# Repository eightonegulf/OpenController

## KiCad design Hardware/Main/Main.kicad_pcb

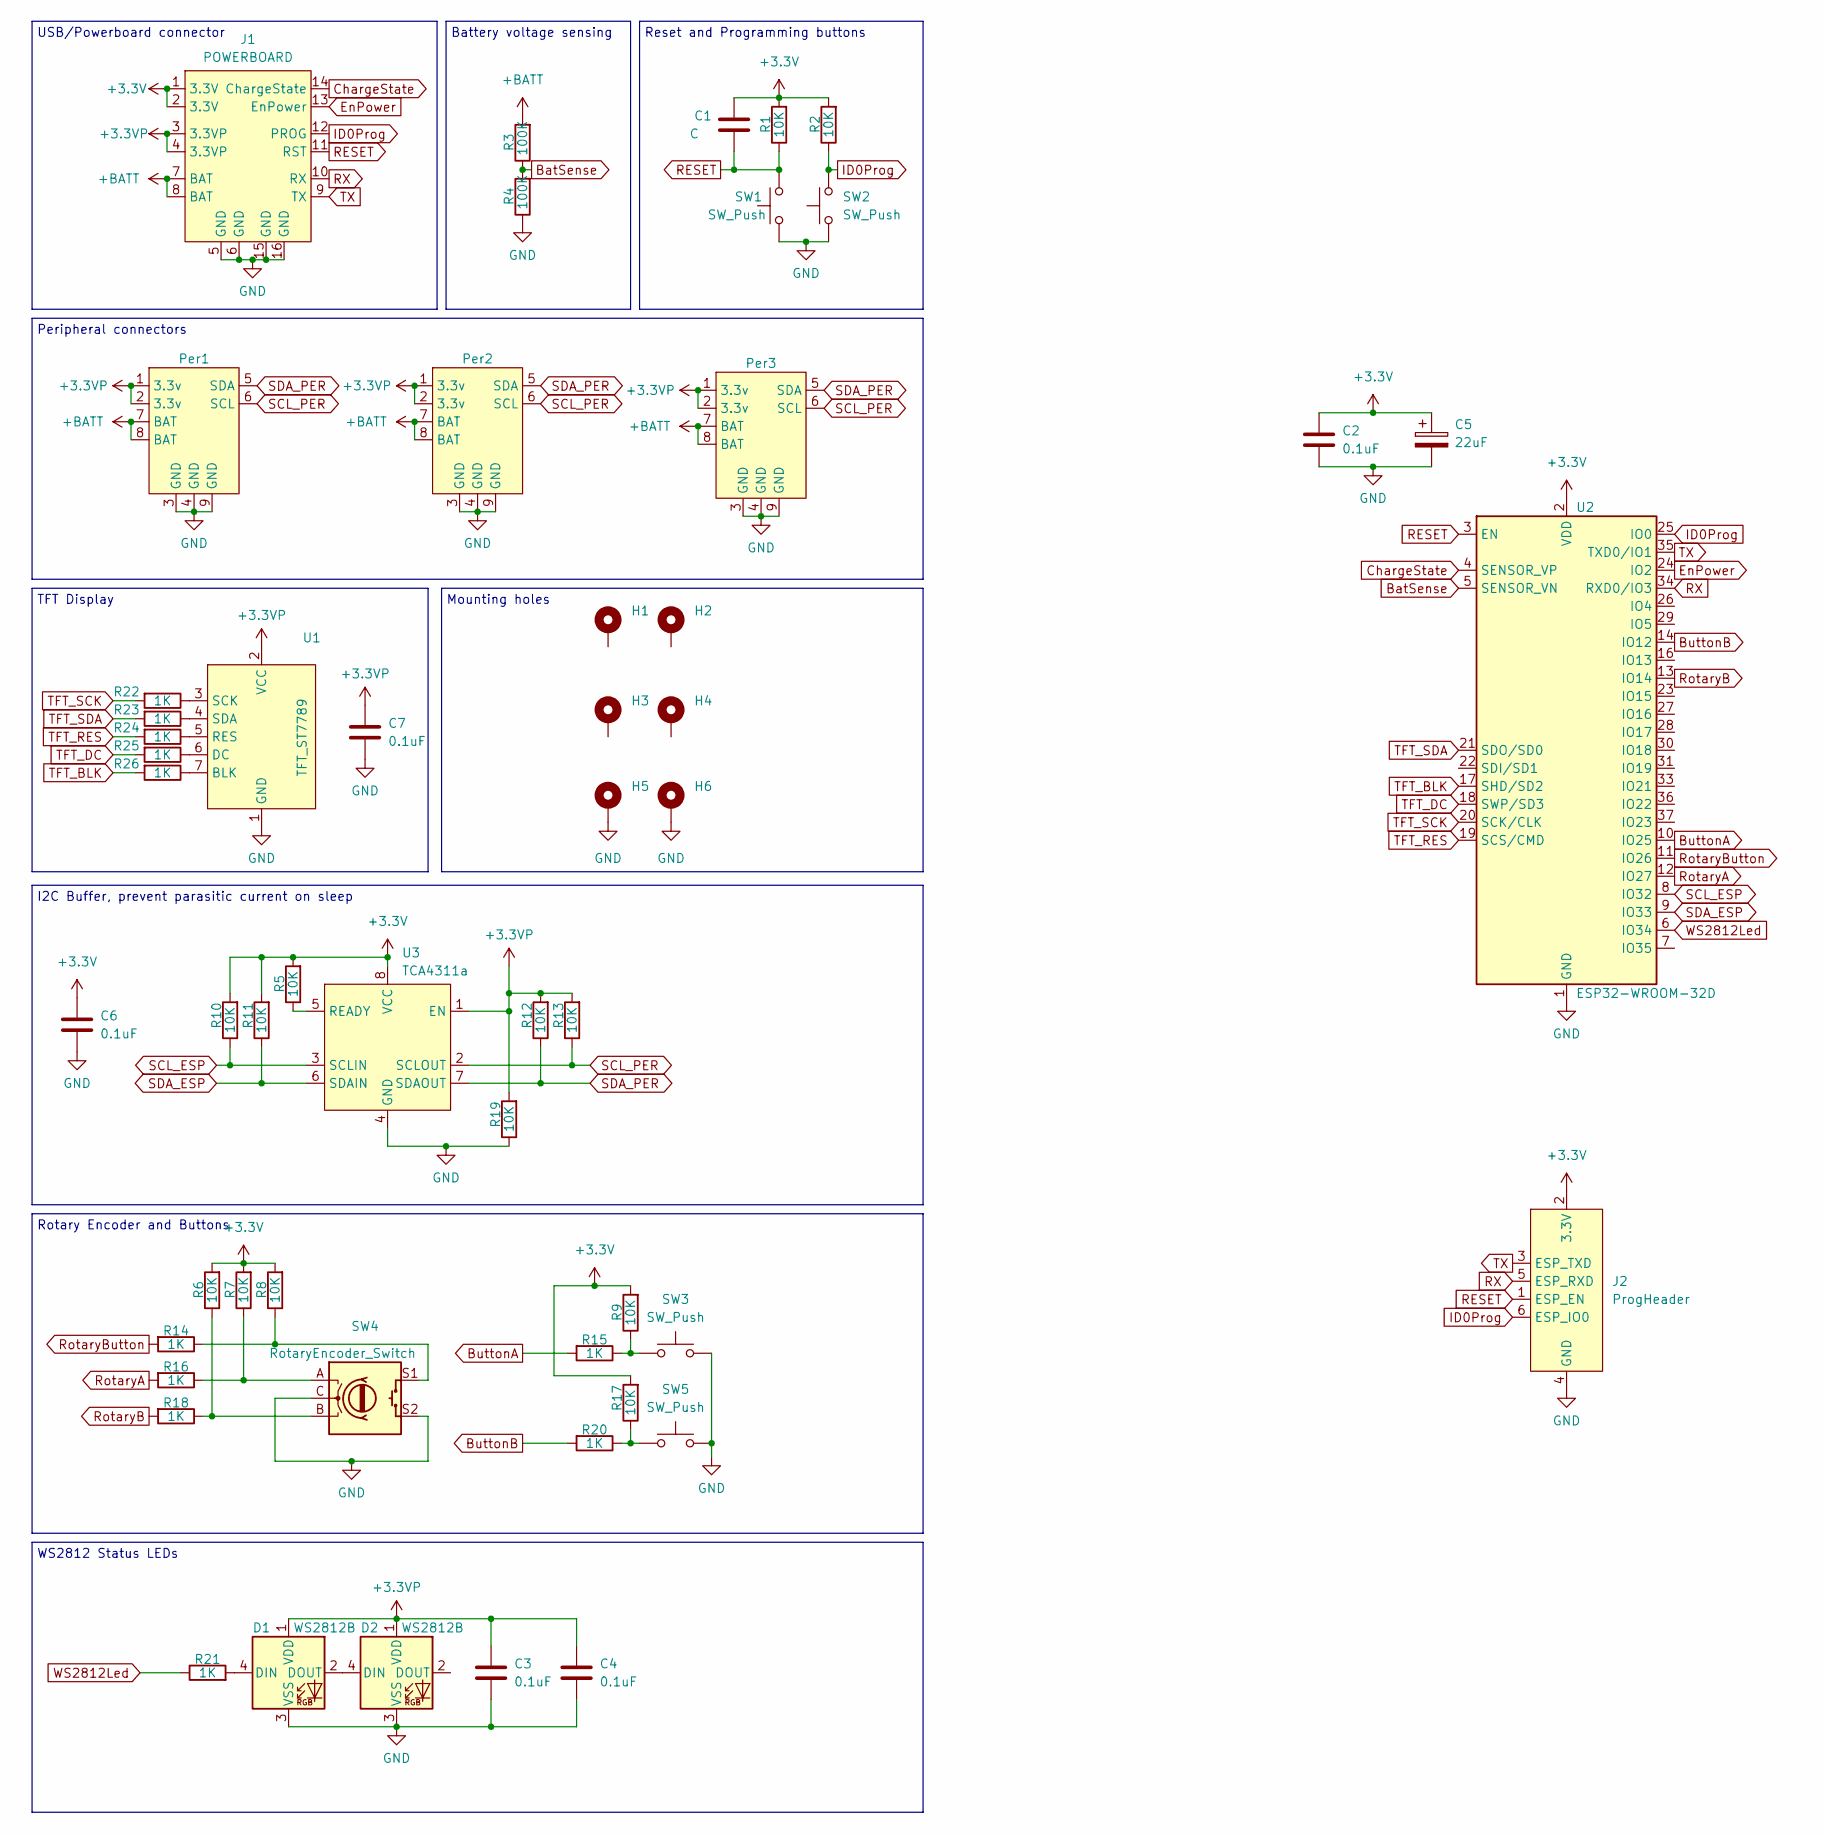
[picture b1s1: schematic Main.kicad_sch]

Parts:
C1: C; C_0805_2012Metric_Pad1.18x1.45mm_HandSolder
C2, C3, C4, C6, C7: 0.1uF; C_0805_2012Metric_Pad1.18x1.45mm_HandSolder
C5: 22uF; CP_Elec_4x5.3
D1, D2: WS2812B; LED_WS2812B_PLCC4_5.0x5.0mm_P3.2mm
H1, H2: MountingHole_Pad; MountingHole_2.2mm_M2_DIN965_Pad
H3, H4, H5, H6: MountingHole_Pad; MountingHole_3.2mm_M3_DIN965_Pad
J1: POWERBOARD; PowerBoardConsumer
J2: ProgHeader; ESP32ProgHeader
Per1: PeripheralMaster
Per2: PeripheralMaster_Right
Per3: PeripheralMaster_Left
R1, R2, R5, R6, R7, R8, R9, R10, R11, R12, R13, R17, R19: 10K; R_0805_2012Metric_Pad1.20x1.40mm_HandSolder
R3, R4: 100K; R_0805_2012Metric_Pad1.20x1.40mm_HandSolder
R14, R15, R16, R18, R20, R21, R22, R23, R24, R25, R26: 1K; R_0805_2012Metric_Pad1.20x1.40mm_HandSolder
SW1, SW2: SW_Push; SW_SPST_TL3305A
SW3, SW5: SW_Push; SW_PUSH_6mm_H8mm
SW4: RotaryEncoder_Switch; RotaryEncoder_Alps_EC11E-Switch_Vertical_H20mm
U1: TFT_ST7789; RGB_TFT_1.3
U2: ESP32-WROOM-32D
U3: TCA4311a; SOIC-8_3.9x4.9mm_P1.27mm

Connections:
+3.3V: C1.2, C2.1, C5.1, C6.1, J1.1 (3.3V), J1.2 (3.3V), J2.2 (3.3V), R1.2, R2.2, R5.2, R6.2, R7.2, R8.2, R9.2, R10.2, R11.2, R17.2, U2.2 (VDD), U3.8 (VCC)
+3.3VP: C3.1, C4.1, C7.1, D1.1 (VDD), D2.1 (VDD), J1.3 (3.3VP), J1.4 (3.3VP), Per1.1 (3.3v), Per1.2 (3.3v), Per2.1 (3.3v), Per2.2 (3.3v), Per3.1 (3.3v), Per3.2 (3.3v), R12.2, R13.2, R19.2, U1.2 (VCC), U3.1 (EN)
+BATT: J1.7 (BAT), J1.8 (BAT), Per1.7 (BAT), Per1.8 (BAT), Per2.7 (BAT), Per2.8 (BAT), Per3.7 (BAT), Per3.8 (BAT), R3.2
BatSense: R3.1, R4.2, U2.5 (SENSOR_VN)
ButtonA: R15.2, U2.10 (IO25)
ButtonB: R20.2, U2.14 (IO12)
ChargeState: J1.14 (ChargeState), U2.4 (SENSOR_VP)
EnPower: J1.13 (EnPower), U2.24 (IO2)
GND: C2.2, C3.2, C4.2, C5.2, C6.2, C7.2, D1.3 (VSS), D2.3 (VSS), H5.1, H6.1, J1.5 (GND), J1.6 (GND), J1.15 (GND), J1.16 (GND), J2.4 (GND), Per1.3 (GND), Per1.4 (GND), Per1.9 (GND), Per2.3 (GND), Per2.4 (GND), Per2.9 (GND), Per3.3 (GND), Per3.4 (GND), Per3.9 (GND), R4.1, R19.1, SW1.1, SW2.1, SW3.2, SW4.C, SW4.S2, SW5.2, U1.1 (GND), U2.1 (GND), U2.15 (GND), U2.38 (GND), U2.39 (GND), U3.4 (GND)
ID0Prog: J1.12 (PROG), J2.6 (ESP_IO0), R2.1, SW2.2, U2.25 (IO0)
unnamed: D1.4 (DIN), R21.2
unnamed: D1.2 (DOUT), D2.4 (DIN)
unnamed: R8.1, R14.1, SW4.S1
unnamed: R9.1, R15.1, SW3.1
unnamed: R7.1, R16.1, SW4.A
unnamed: R17.1, R20.1, SW5.1
unnamed: R6.1, R18.1, SW4.B
unnamed: R26.1, U1.7 (BLK)
unnamed: R25.1, U1.6 (DC)
unnamed: R24.1, U1.5 (RES)
unnamed: R22.1, U1.3 (SCK)
unnamed: R23.1, U1.4 (SDA)
unnamed: R5.1, U3.5 (READY)
RESET: C1.1, J1.11 (RST), J2.1 (ESP_EN), R1.1, SW1.2, U2.3 (EN)
RX: J1.10 (RX), J2.5 (ESP_RXD), U2.34 (RXD0/IO3)
RotaryA: R16.2, U2.12 (IO27)
RotaryB: R18.2, U2.13 (IO14)
RotaryButton: R14.2, U2.11 (IO26)
SCL_ESP: R10.1, U2.8 (IO32), U3.3 (SCLIN)
SCL_PER: Per1.6 (SCL), Per2.6 (SCL), Per3.6 (SCL), R13.1, U3.2 (SCLOUT)
SDA_ESP: R11.1, U2.9 (IO33), U3.6 (SDAIN)
SDA_PER: Per1.5 (SDA), Per2.5 (SDA), Per3.5 (SDA), R12.1, U3.7 (SDAOUT)
TFT_BLK: R26.2, U2.17 (SHD/SD2)
TFT_DC: R25.2, U2.18 (SWP/SD3)
TFT_RES: R24.2, U2.19 (SCS/CMD)
TFT_SCK: R22.2, U2.20 (SCK/CLK)
TFT_SDA: R23.2, U2.21 (SDO/SD0)
TX: J1.9 (TX), J2.3 (ESP_TXD), U2.35 (TXD0/IO1)
WS2812Led: R21.1, U2.6 (IO34)

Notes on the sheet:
Mounting holes
Peripheral connectors
Reset and Programming buttons
WS2812 Status LEDs
TFT Display
I2C Buffer, prevent parasitic current on sleep
USB/Powerboard connector
Rotary Encoder and Buttons
Battery voltage sensing

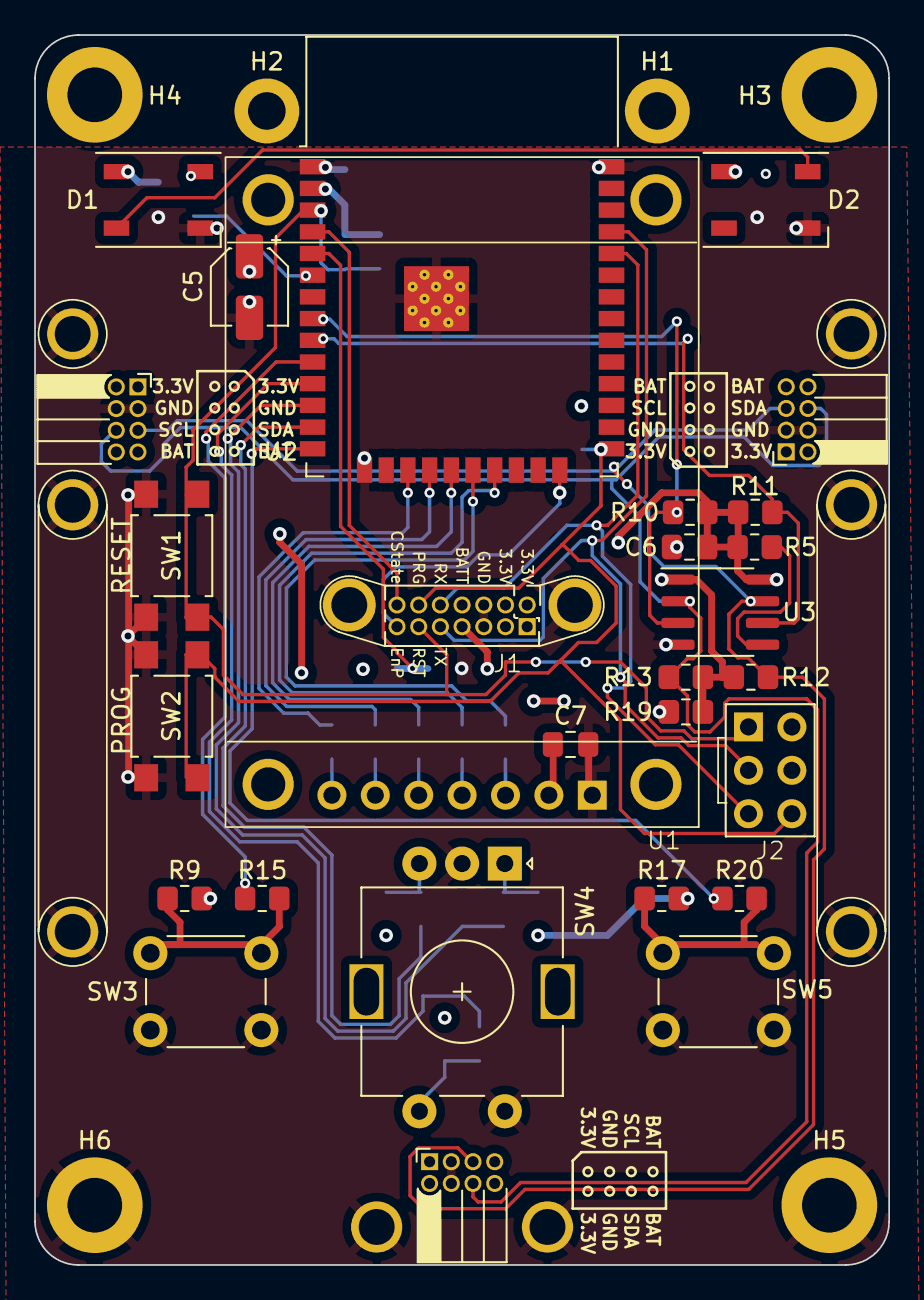
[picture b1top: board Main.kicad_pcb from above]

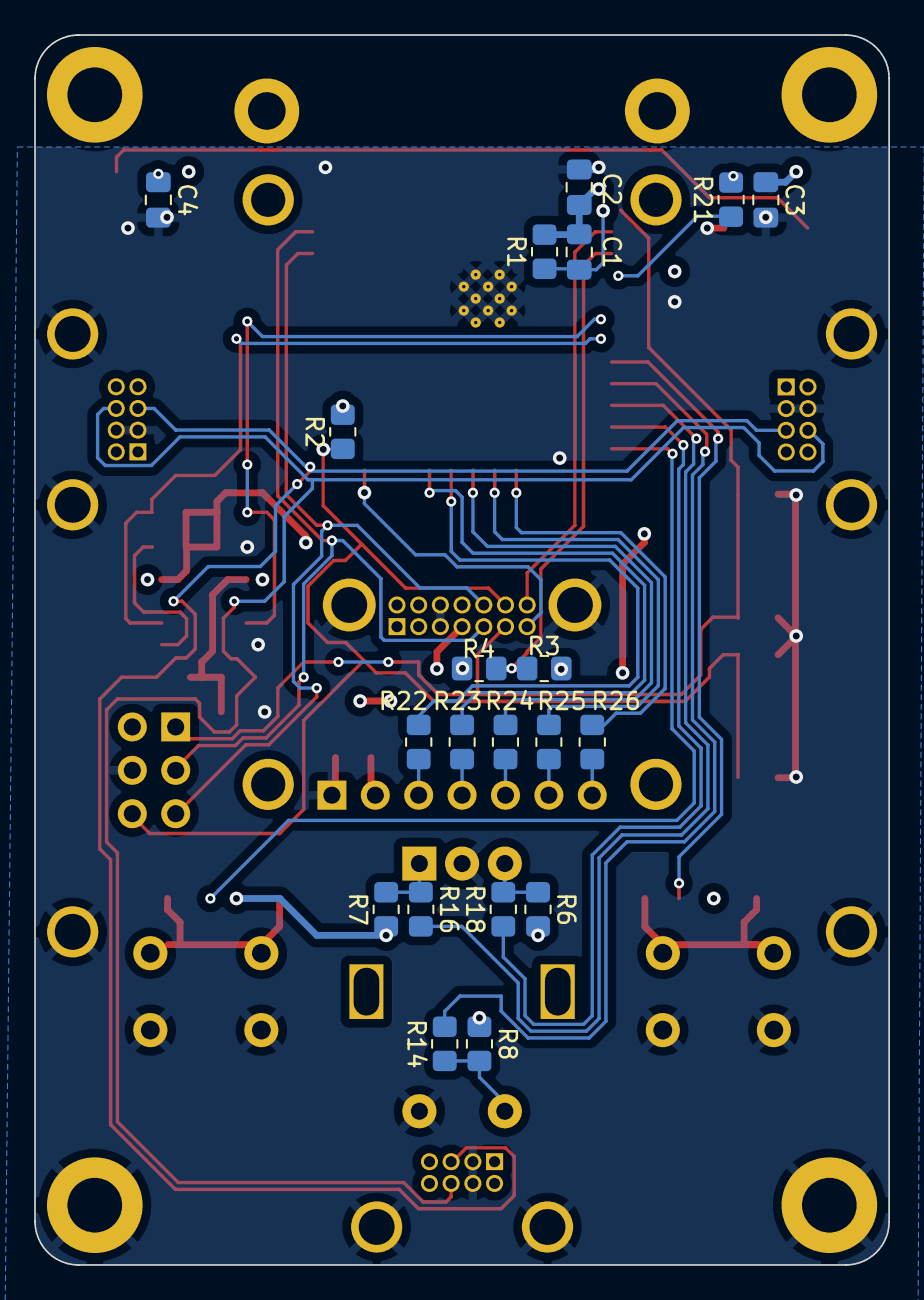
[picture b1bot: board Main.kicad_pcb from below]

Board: 4 copper layers, 50.0 x 72.0 mm, 54 parts (20 on the bottom side), 39 nets.

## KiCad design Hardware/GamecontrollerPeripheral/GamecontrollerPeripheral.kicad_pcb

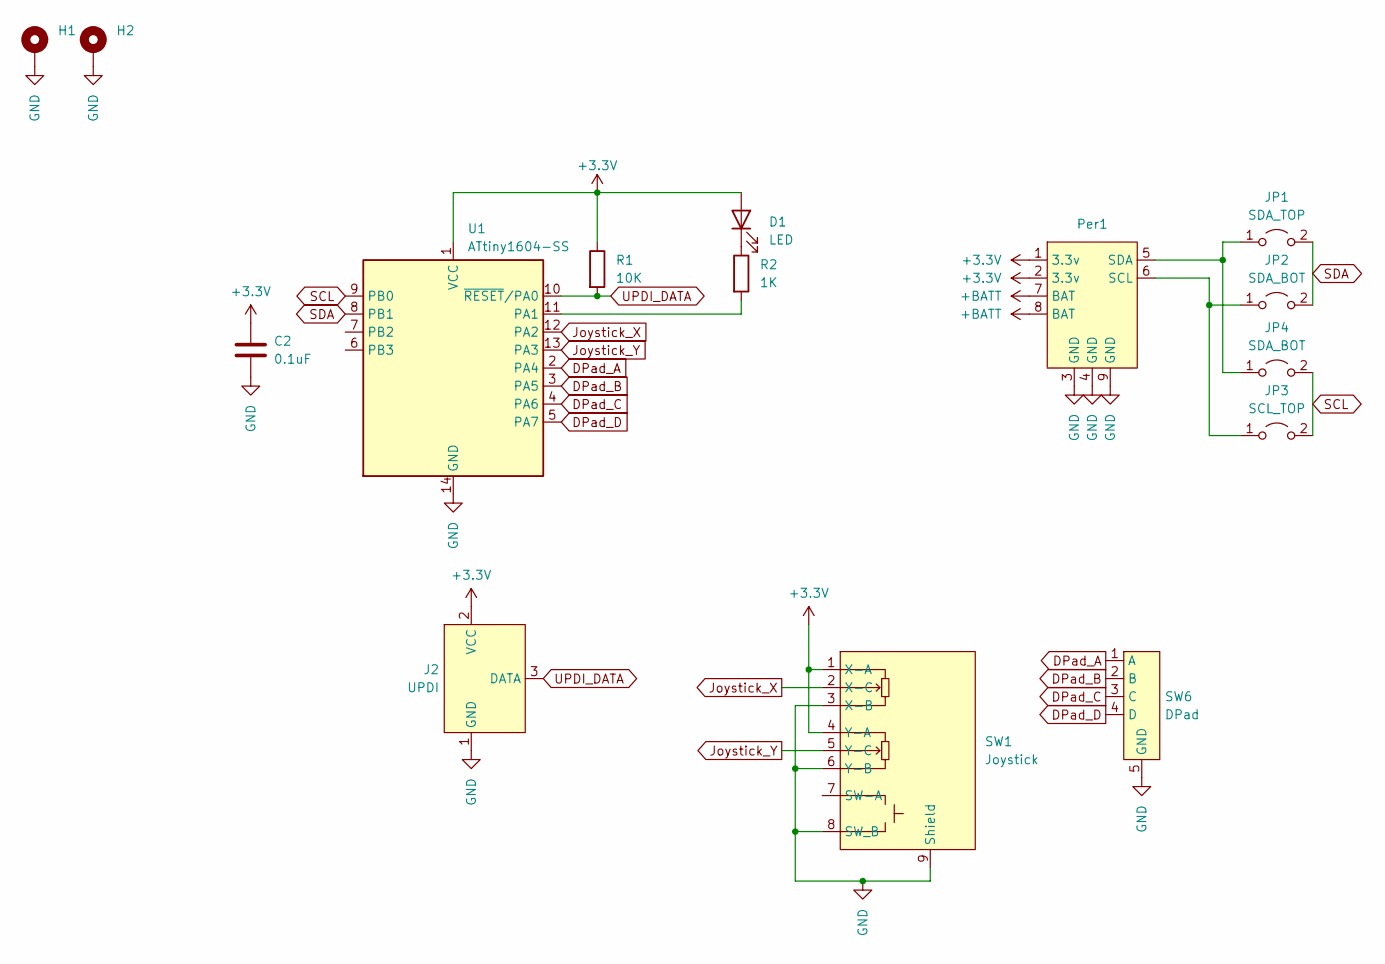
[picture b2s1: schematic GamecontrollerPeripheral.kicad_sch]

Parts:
C2: 0.1uF; C_0805_2012Metric_Pad1.18x1.45mm_HandSolder
D1: LED; LED_0805_2012Metric_Pad1.15x1.40mm_HandSolder
H1, H2: MountingHole_Pad; MountingHole_2.2mm_M2_DIN965_Pad
J2: UPDI; PinHeader_1x03_P2.54mm_Vertical
JP1: SDA_TOP; SolderJumper-2_P1.3mm_Open_RoundedPad1.0x1.5mm
JP2, JP4: SDA_BOT; SolderJumper-2_P1.3mm_Open_RoundedPad1.0x1.5mm
JP3: SCL_TOP; SolderJumper-2_P1.3mm_Open_RoundedPad1.0x1.5mm
Per1: PeripheralSlave
R1: 10K; R_0805_2012Metric_Pad1.20x1.40mm_HandSolder
R2: 1K; R_0805_2012Metric_Pad1.20x1.40mm_HandSolder
SW1: Joystick; Joystick-Universal
SW6: DPad; D-Pad
U1: ATtiny1604-SS; SOIC-14_3.9x8.7mm_P1.27mm

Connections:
+3.3V: D1.2 (A), J2.2 (VCC), Per1.1 (3.3v), Per1.2 (3.3v), R1.1, SW1.1 (X-A), SW1.4 (Y-A), U1.1 (VCC); also elsewhere on the board
+BATT: Per1.7 (BAT), Per1.8 (BAT)
DPad_A: SW6.1 (A), U1.2 (PA4)
DPad_B: SW6.2 (B), U1.3 (PA5)
DPad_C: SW6.3 (C), U1.4 (PA6)
DPad_D: SW6.4 (D), U1.5 (PA7)
GND: H1.1, H2.1, J2.1 (GND), Per1.3 (GND), Per1.4 (GND), Per1.9 (GND), SW1.3 (X-B), SW1.6 (Y-B), SW1.8 (SW_B), SW1.9 (Shield), SW6.5 (GND), U1.14 (GND); also elsewhere on the board
Joystick_X: SW1.2 (X-C), U1.12 (PA2)
Joystick_Y: SW1.5 (Y-C), U1.13 (PA3)
unnamed: D1.1 (K), R2.1
unnamed: JP1.1 (A), JP4.1 (A), Per1.5 (SDA)
unnamed: JP2.1 (A), JP3.1 (A), Per1.6 (SCL)
unnamed: R2.2, U1.11 (PA1)
SCL: JP3.2 (B), JP4.2 (B), U1.9 (PB0)
SDA: JP1.2 (B), JP2.2 (B), U1.8 (PB1)
UPDI_DATA: J2.3 (DATA), R1.2, U1.10 (~RESET/PA0)

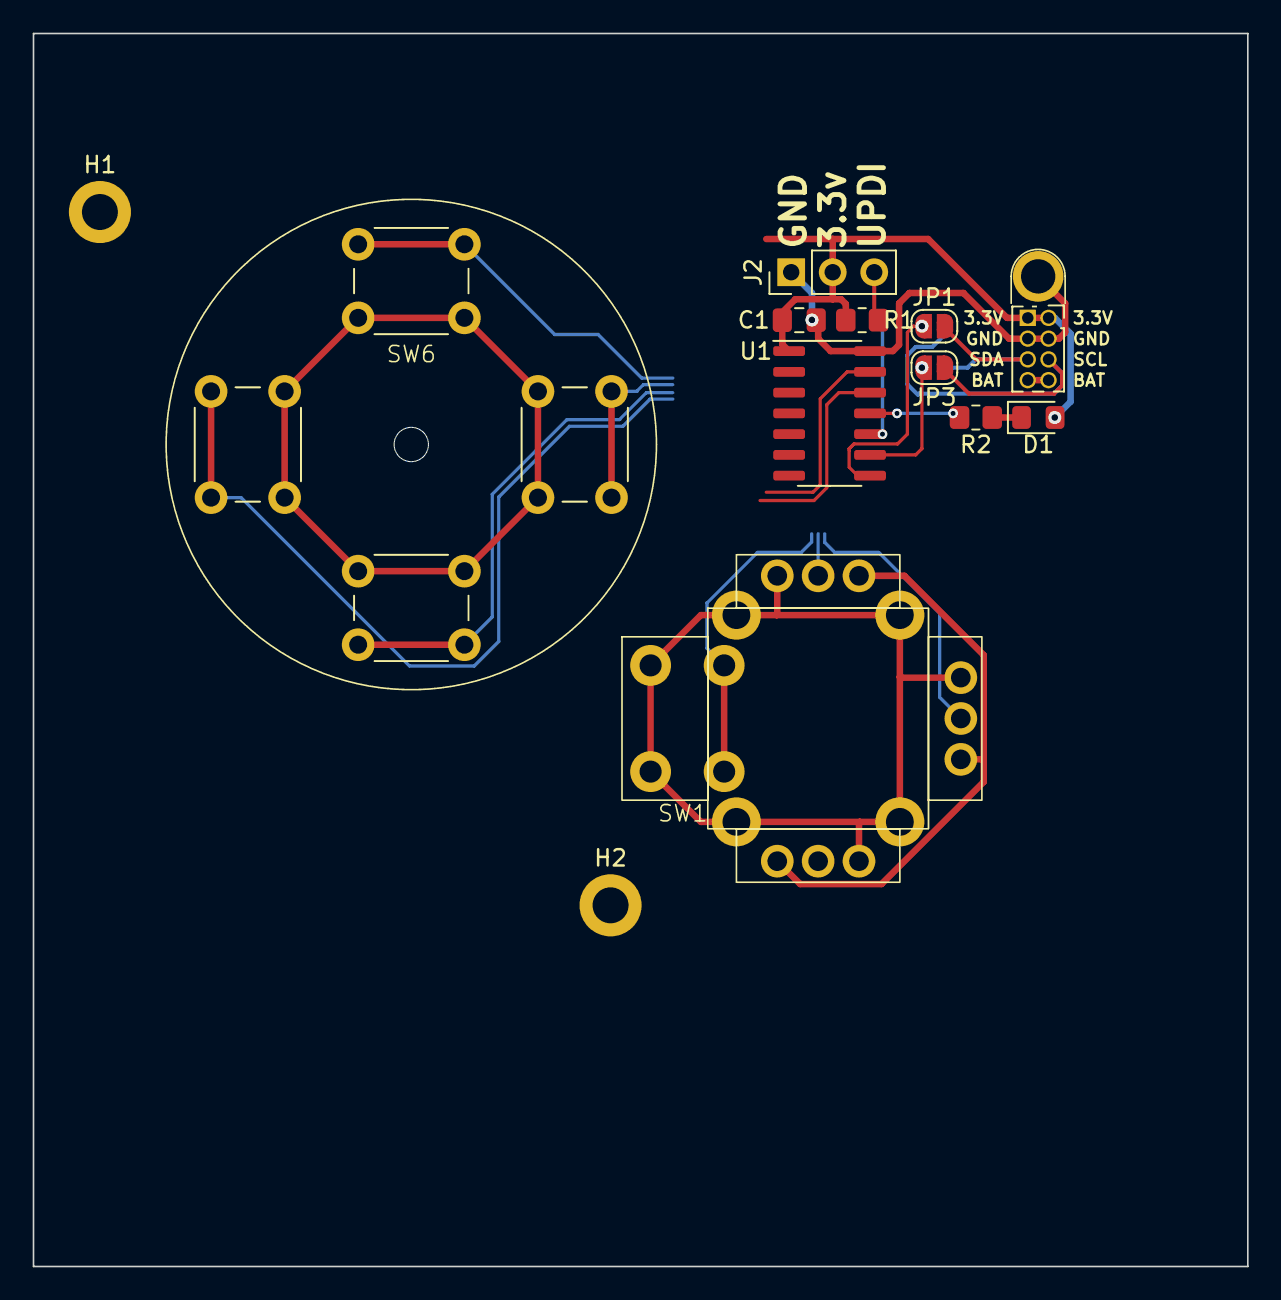
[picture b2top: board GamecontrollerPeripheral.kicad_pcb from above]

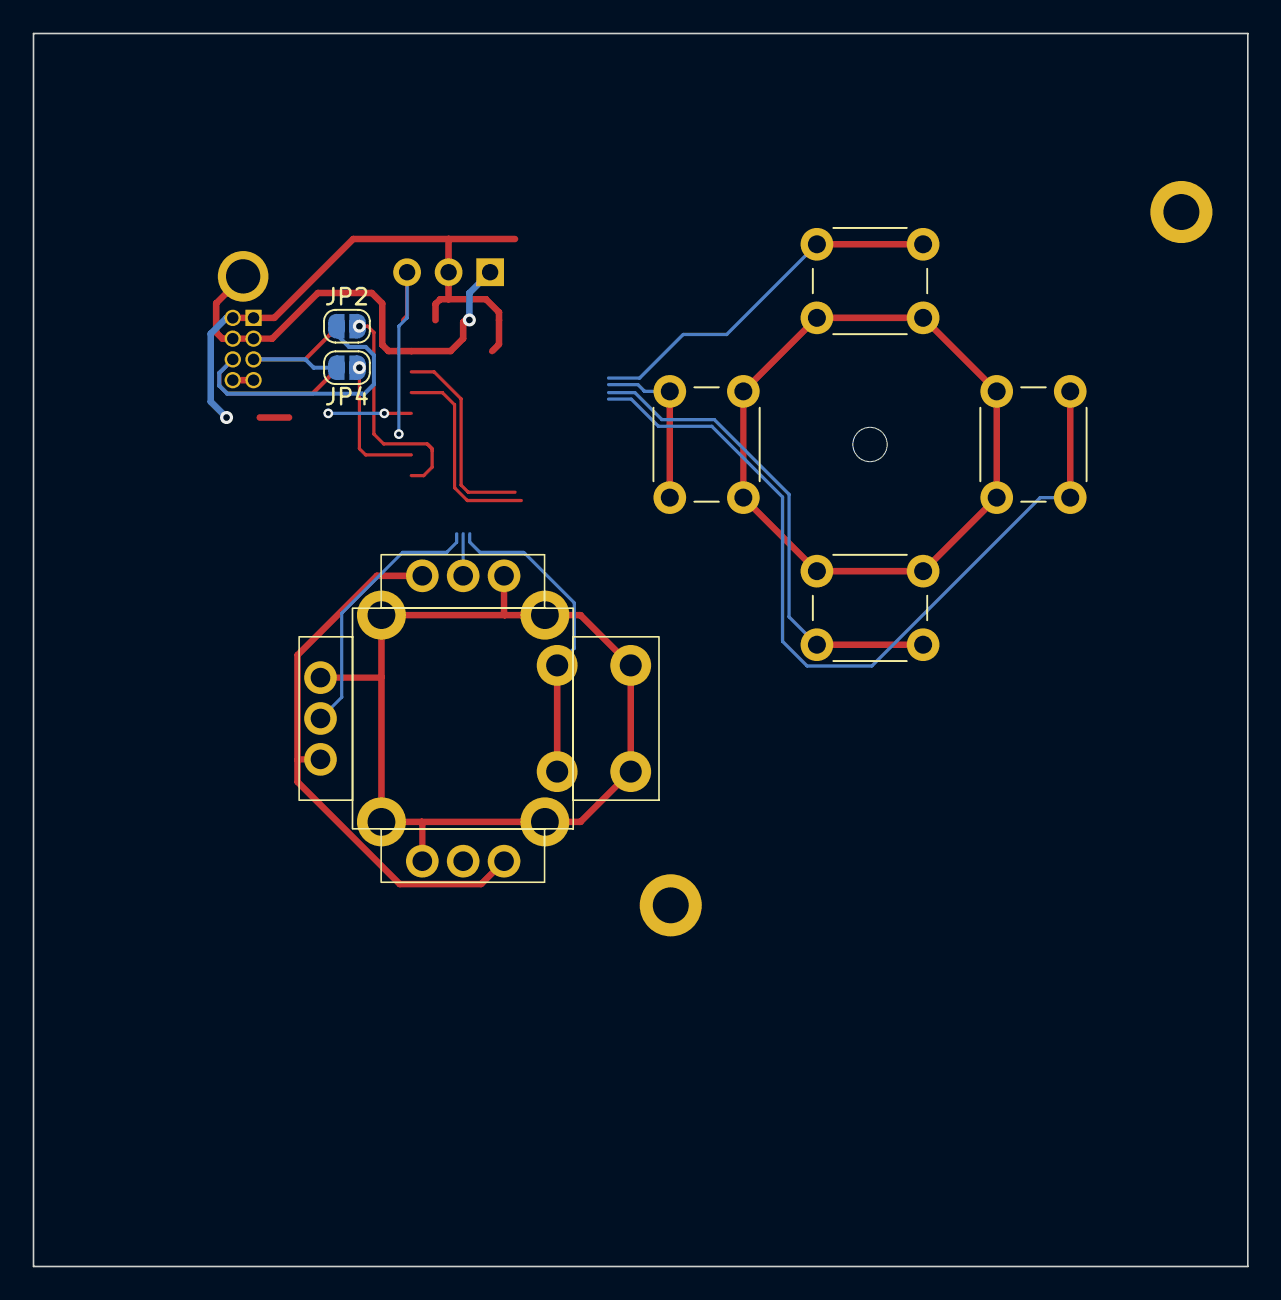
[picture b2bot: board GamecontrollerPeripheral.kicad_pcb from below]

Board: 2 copper layers, 74.3 x 75.4 mm, 15 parts (2 on the bottom side), 16 nets.

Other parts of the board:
C1: 0.1uF; C_0805_2012Metric_Pad1.18x1.45mm_HandSolder

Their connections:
+3.3V: C1.1; also elsewhere on the board
GND: C1.2; also elsewhere on the board

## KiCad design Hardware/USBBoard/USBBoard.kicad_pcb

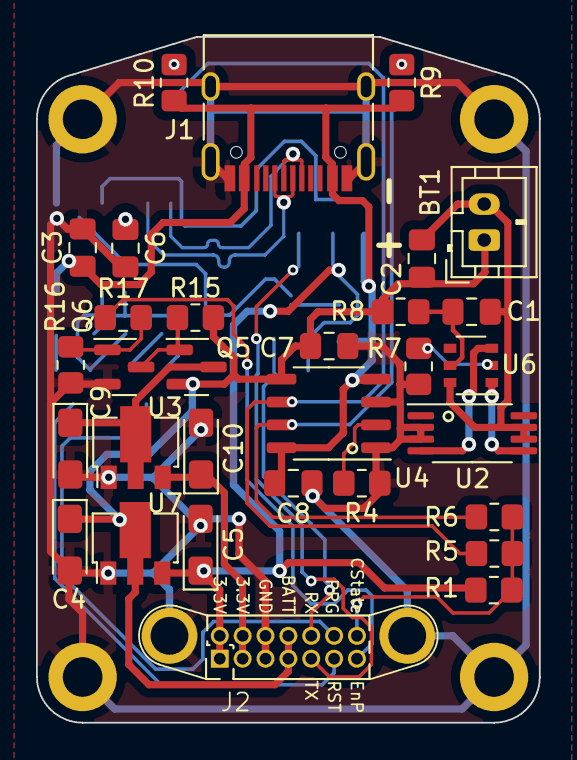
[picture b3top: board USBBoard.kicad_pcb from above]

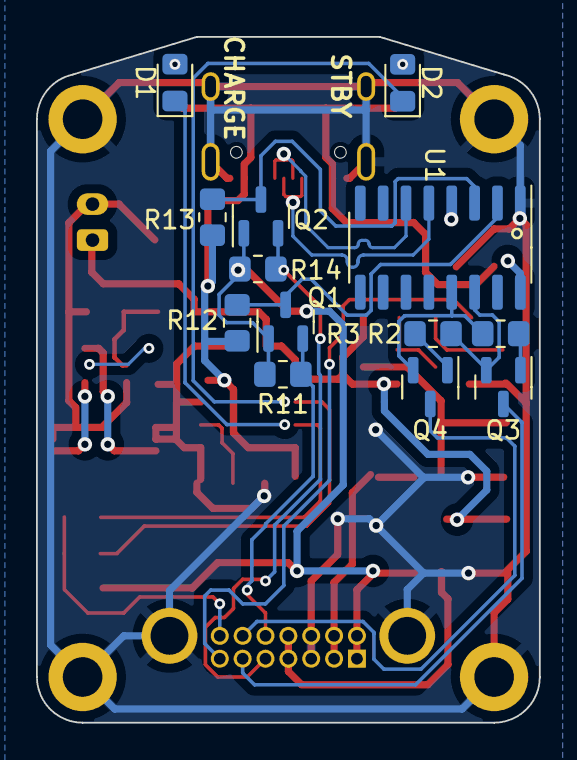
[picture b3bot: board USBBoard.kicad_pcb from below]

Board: 2 copper layers, 27.9 x 38.1 mm, 48 parts (13 on the bottom side), 33 nets.

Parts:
BT1: Battery_Cell; JST_PH_B2B-PH-K_1x02_P2.00mm_Vertical
C1: 100nF; C_0805_2012Metric_Pad1.18x1.45mm_HandSolder
C2, C7, C8: 10uF; C_0805_2012Metric_Pad1.18x1.45mm_HandSolder
C3, C6: 0.1uF; C_0805_2012Metric_Pad1.18x1.45mm_HandSolder
C4, C5, C9, C10: 1uF Tantalum; CP_EIA-3216-18_Kemet-A_Pad1.58x1.35mm_HandSolder
D1: CHARGE; D_0805_2012Metric_Pad1.15x1.40mm_HandSolder
D2: STBY; D_0805_2012Metric_Pad1.15x1.40mm_HandSolder
H1, H2, H3, H4: MountingHole_Pad; MountingHole_2.2mm_M2_DIN965_Pad
J1: USB_C_Receptacle_USB2.0; USB_C_Receptacle_HRO_TYPE-C-31-M-12
J2: POWERBOARD; PowerBoard
Q1, Q2: BS170F; SOT-23
Q3, Q4: BC846; SOT-23
Q5: AO3401A; SOT-23
Q6: 2N7002; SOT-23
R1, R5: 50K; R_0805_2012Metric_Pad1.20x1.40mm_HandSolder
R2, R3, R11, R12, R13, R14: 12K; R_0805_2012Metric_Pad1.20x1.40mm_HandSolder
R4: R; R_0805_2012Metric_Pad1.20x1.40mm_HandSolder
R6: 25K; R_0805_2012Metric_Pad1.20x1.40mm_HandSolder
R7, R9, R10, R17: 1K; R_0805_2012Metric_Pad1.20x1.40mm_HandSolder
R8: 100; R_0805_2012Metric_Pad1.20x1.40mm_HandSolder
R15, R16: 10K; R_0805_2012Metric_Pad1.20x1.40mm_HandSolder
U1: CH340C; SOIC-16_3.9x9.9mm_P1.27mm
U2: FS8205A; TSSOP-8_4.4x3mm_P0.65mm
U3, U7: XC6203; SOT-89-3
U4: TC4056A; SOP-8_3.9x4.9mm_P1.27mm
U6: DW01-P; TSOP-6_1.65x3.05mm_P0.95mm

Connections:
+3.3V: C5.1, J2.1 (3.3V), J2.2 (3.3V), Q1.1 (G), Q2.1 (G), R1.2, R11.2, R14.2, U7.3 (VOUT)
+3.3VP: C10.1, J2.3 (3.3VP), J2.4 (3.3VP), U3.3 (VOUT)
+5V: C3.1, C8.2, J1.A4 (VBUS), J1.A9 (VBUS), J1.B4 (VBUS), J1.B9 (VBUS), R9.2, R10.2, R12.2, R13.2, U1.16 (VCC), U4.4 (VCC), U4.8 (CE)
+BATT: BT1.1 (+), C2.1, C4.1, C7.1, J2.7 (BAT), J2.8 (BAT), Q5.2 (S), R8.1, R15.2, U4.5 (BAT), U7.2 (VIN)
-BATT: BT1.2 (-), C1.2, C2.2, U2.6 (S2), U2.7 (S2), U6.6 (GND)
ChargeState: J2.14 (ChargeState), R1.1, R5.2, R6.2
EnPower: J2.13 (EnPower), R17.2
GND: C3.2, C4.2, C5.2, C6.2, C7.2, C8.1, C9.2, C10.2, H1.1, H2.1, H3.1, H4.1, J1.A1 (GND), J1.A12 (GND), J1.B1 (GND), J1.B12 (GND), J1.S1 (SHIELD), J2.5 (GND), J2.6 (GND), J2.15 (GND), J2.16 (GND), Q6.2 (S), R4.2, R7.1, R16.1, U1.1 (GND), U2.2 (S1), U2.3 (S1), U3.1 (GND), U4.1 (TEMP), U4.3 (GND), U7.1 (GND)
unnamed: D1.2 (A), R9.1
unnamed: D2.2 (A), R10.1
unnamed: Q1.3 (D), R12.1, U1.2 (TXD)
unnamed: Q2.3 (D), R13.1, U1.3 (RXD)
unnamed: Q3.1 (B), R2.2
unnamed: Q3.2 (E), R3.1, U1.14 (~RTS)
unnamed: Q4.1 (B), R3.2
unnamed: Q4.2 (E), R2.1, U1.13 (~DTR)
unnamed: C9.1, Q5.3 (D), U3.2 (VIN)
unnamed: Q5.1 (G), Q6.3 (D), R15.1
unnamed: Q6.1 (G), R16.2, R17.1
unnamed: C6.1, U1.4 (V3)
unnamed: U2.4 (G1), U6.3 (OC)
unnamed: U2.5 (G2), U6.1 (OD)
unnamed: R4.1, U4.2 (PROG)
unnamed: R7.2, U6.2 (CS)
unnamed: C1.1, R8.2, U6.5 (VCC)
STATE_CHARGE: D1.1 (K), R6.1, U4.7 (CHARGE)
STATE_STBY: D2.1 (K), R5.1, U4.6 (STBY)
UC_EN: J2.11 (RST), Q3.3 (C)
UC_ID0: J2.12 (PROG), Q4.3 (C)
UC_RX: J2.10 (RX), Q1.2 (S), R11.1
UC_TX: J2.9 (TX), Q2.2 (S), R14.1
USB_D+: J1.A6 (D+), J1.B6 (D+), U1.5 (UD+)
USB_D-: J1.A7 (D-), J1.B7 (D-), U1.6 (UD-)

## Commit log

2024-09-11 .gitignore
2024-09-11 Initial design in progress
2024-09-11 Fix grouping issue on USBBoard
2024-09-11 UPDI Connector
2024-09-11 GamecontrollerPeripheral
2024-09-12 XC6203 & DW01-P part library
2024-09-12 InputDevices library
2024-09-12 GamecontrollerPeripheral progres
2024-09-12 USBBoard complete
2024-09-12 Library paths relative instead of absolute
2024-09-12 Mainboard edge cuts
2024-09-13 USBBoard tweaks
2024-09-13 Mainboard routing etc
2024-09-13 3D Models initial
2024-09-13 2.56 header and socket models
2024-09-13 TFT display model
2024-09-13 Use TFT display in mainboard model
2024-09-13 DPad model
2024-09-15 ESP32 programming header component
2024-09-15 TFT keepout areas
2024-09-15 Progress with main board
2024-09-15 Fix Powerboard connectors courtyard
2024-09-15 Remove labels
2024-09-15 Mainboard r0.1
2024-09-17 Need to make more commits; Changed design to use horizontal peripheral connectors. Changed models, more compact design. Still in progress
2024-09-17 Some margins. Support for buttons and rotary encoder
2024-09-17 Colors
2024-09-17 Button springs
2024-09-18 Apply Button springs
2024-09-18 Sink main PCB into case
2024-09-18 Case midpart walls, join with top
2024-09-18 Exploded view
2024-09-18 USB port to case
2024-09-18 Rounded case edges
2024-09-18 Lightpipes
2024-09-18 Better resolution on bolt holes Bottom peripheral cutout
2024-09-18 Peripheral cutout trimming
2024-09-18 Button indent
2024-09-18 Cleanup output
2024-09-18 Smaller mainboard pillars
2024-09-18 PCBBoard connector to other side of board
2024-09-18 Add extra mountingscrew to side peripherals
